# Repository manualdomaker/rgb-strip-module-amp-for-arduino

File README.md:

# RAUL HACKER CLUB - rgb-strip-module-amp-for-arduino

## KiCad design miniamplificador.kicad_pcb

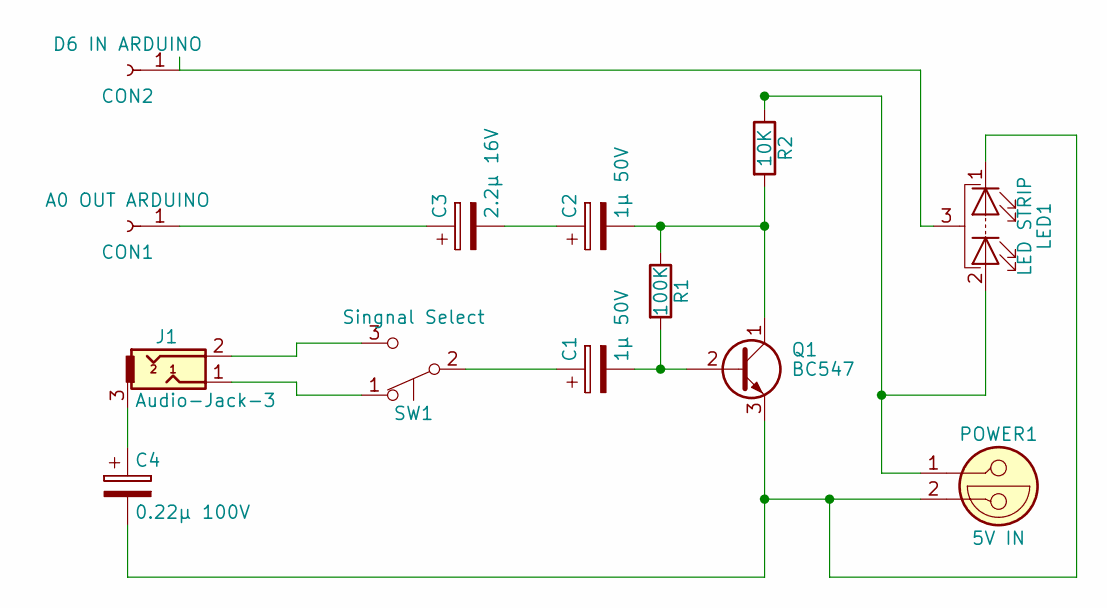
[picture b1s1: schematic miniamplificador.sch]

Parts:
C1, C2: 1μ 50V; CP_Radial_D4.0mm_P2.00mm
C3: 2.2μ 16V; CP_Radial_D4.0mm_P2.00mm
C4: 0.22μ 100V; CP_Radial_D4.0mm_P2.00mm
CON1: A0 OUT ARDUINO; Socket_Strip_Straight_1x01_Pitch2.54mm
CON2: D6 IN ARDUINO; Socket_Strip_Straight_1x01_Pitch2.54mm
J1: Audio-Jack-3; Molex_KK-41791-03_03x3.96mm_Straight
LED1: LED STRIP; LED_Rectangular_W5.0mm_H2.0mm-3pins
POWER1: 5V IN; JACK_ALIM
Q1: BC547; TO-92_Molded_Narrow
R1: 100K; R_Axial_DIN0309_L9.0mm_D3.2mm_P12.70mm_Horizontal
R2: 10K; R_Axial_DIN0309_L9.0mm_D3.2mm_P12.70mm_Horizontal
SW1: Singnal Select; SW_NKK_G1xJP

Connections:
unnamed: C1.1, SW1.2 (B)
unnamed: C1.2, Q1.2 (B), R1.2
unnamed: C2.1, C3.2
unnamed: C2.2, Q1.1 (C), R1.1, R2.2
unnamed: C3.1, CON1.1
unnamed: C4.1, J1.3
unnamed: C4.2, LED1.1 (K), POWER1.2, Q1.3 (E)
unnamed: CON2.1, LED1.3 (PAD)
unnamed: J1.1, SW1.1 (A)
unnamed: J1.2, SW1.3 (C)
unnamed: LED1.2 (A), POWER1.1, R2.1

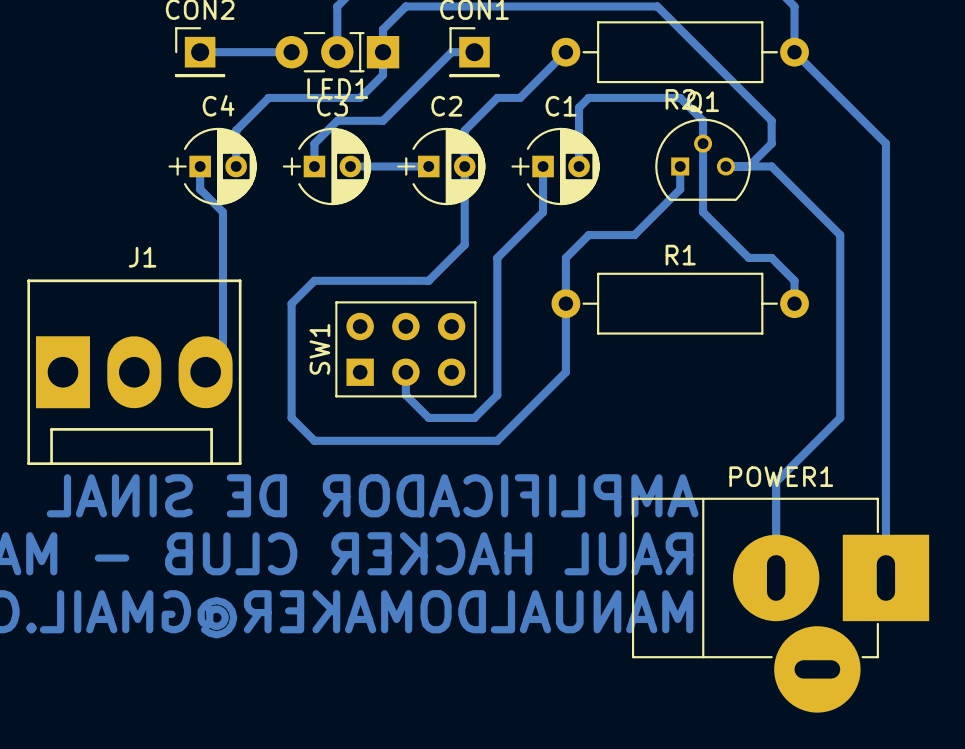
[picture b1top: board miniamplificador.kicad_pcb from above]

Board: 2 copper layers, 13 parts (0 on the bottom side), 11 nets.

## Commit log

2020-01-01 Adicionado arquivos do Kicad
    Olá a todos.
    Compartilho estes aquivos para a comunidade.
    Trata-se de um simples amplificador de sinal, e neste caso o sinal seria o áudio de uma música para que o arduino capture o mesmo e faça a "conversão" do sinal para controlar uma fita de led.
    Caso encontre alguma melhoria no código wiring ou do kicad, ficaremos todos gratos.
    Espero que gostem! :-)
2020-01-01 Arquivo do arduino
2020-01-01 Imagens
2020-01-01 Fechamento das trilhas da placa
